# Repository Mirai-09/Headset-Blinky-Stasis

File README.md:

# Headset-Blinky-Stasis
This is Headset blinky that I made using a guide on Stasis, A YSWS from Hack Club!  

I made the PCB in the shape of Headset to match the Cassette PCB that I made before!

# Schematic!

# PCB!
Front: <br>

Back: <br>

3D: <br>

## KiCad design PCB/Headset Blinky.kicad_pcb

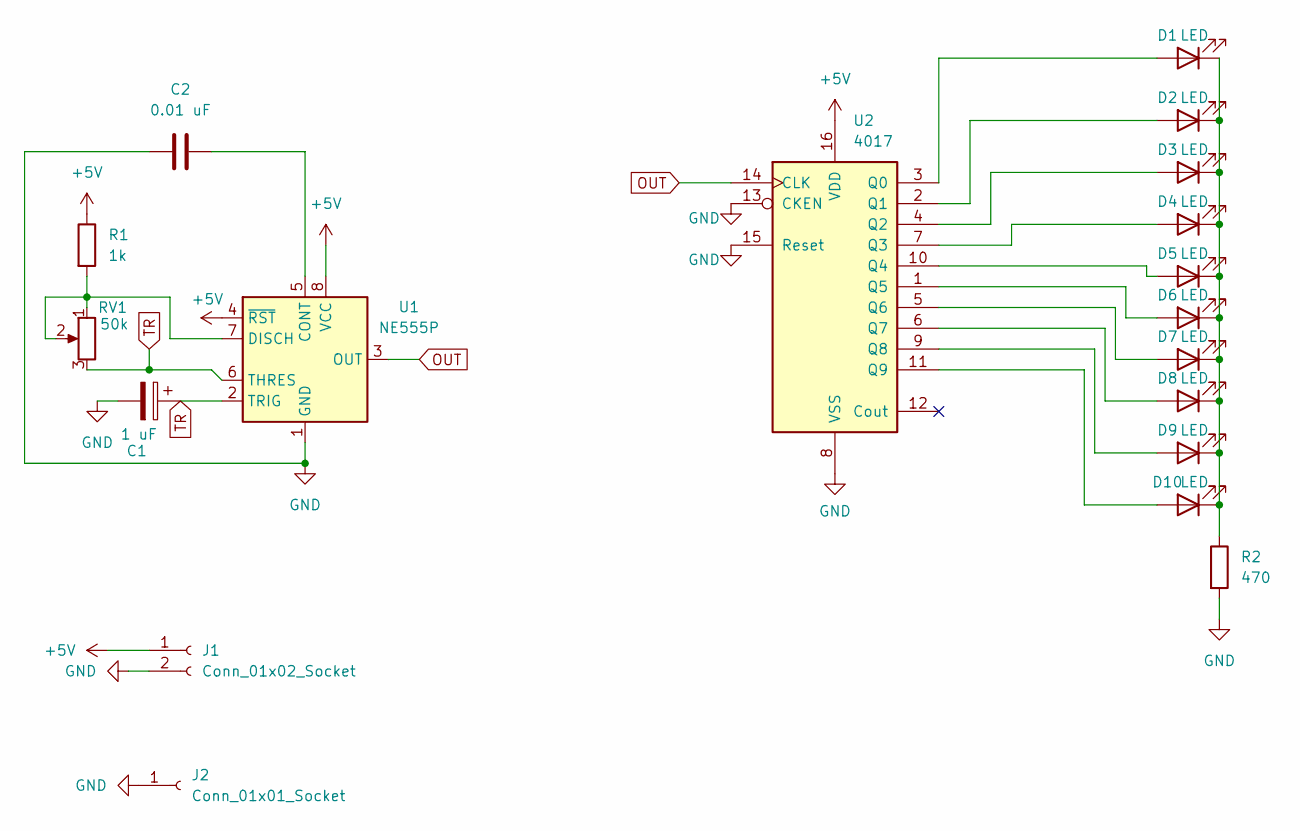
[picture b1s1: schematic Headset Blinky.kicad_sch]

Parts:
C1: 1 uF; CP_Radial_D5.0mm_P2.00mm
C2: 0.01 uF; C_Disc_D7.0mm_W2.5mm_P5.00mm
D1, D2, D3, D4, D5, D6, D7, D8, D9, D10: LED; LED_D3.0mm
J1: Conn_01x02_Socket; PinHeader_1x02_P2.54mm_Vertical
J2: Conn_01x01_Socket; PinHeader_1x01_P2.54mm_Vertical
R1: 1k; R_Axial_DIN0207_L6.3mm_D2.5mm_P7.62mm_Horizontal
R2: 470; R_Axial_DIN0207_L6.3mm_D2.5mm_P7.62mm_Horizontal
RV1: 50k; Potentiometer_Vishay_T93YA_Vertical
U1: NE555P; DIP-8_W7.62mm
U2: 4017; N16

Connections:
+5V: J1.1, R1.1, U1.4 (~RST), U1.8 (VCC), U2.16 (VDD)
GND: C1.2, C2.1, J1.2, J2.1, R2.2, U1.1 (GND), U2.8 (VSS), U2.13 (CKEN), U2.15 (Reset)
unnamed: D1.2 (A), U2.3 (Q0)
unnamed: D1.1 (K), D2.1 (K), D3.1 (K), D4.1 (K), D5.1 (K), D6.1 (K), D7.1 (K), D8.1 (K), D9.1 (K), D10.1 (K), R2.1
unnamed: D2.2 (A), U2.2 (Q1)
unnamed: D3.2 (A), U2.4 (Q2)
unnamed: D4.2 (A), U2.7 (Q3)
unnamed: D5.2 (A), U2.10 (Q4)
unnamed: D6.2 (A), U2.1 (Q5)
unnamed: D7.2 (A), U2.5 (Q6)
unnamed: D8.2 (A), U2.6 (Q7)
unnamed: D9.2 (A), U2.9 (Q8)
unnamed: D10.2 (A), U2.11 (Q9)
unnamed: C2.2, U1.5 (CONT)
unnamed: R1.2, RV1.1, RV1.2, U1.7 (DISCH)
OUT: U1.3 (OUT), U2.14 (CLK)
TR: C1.1, RV1.3, U1.2 (TRIG), U1.6 (THRES)

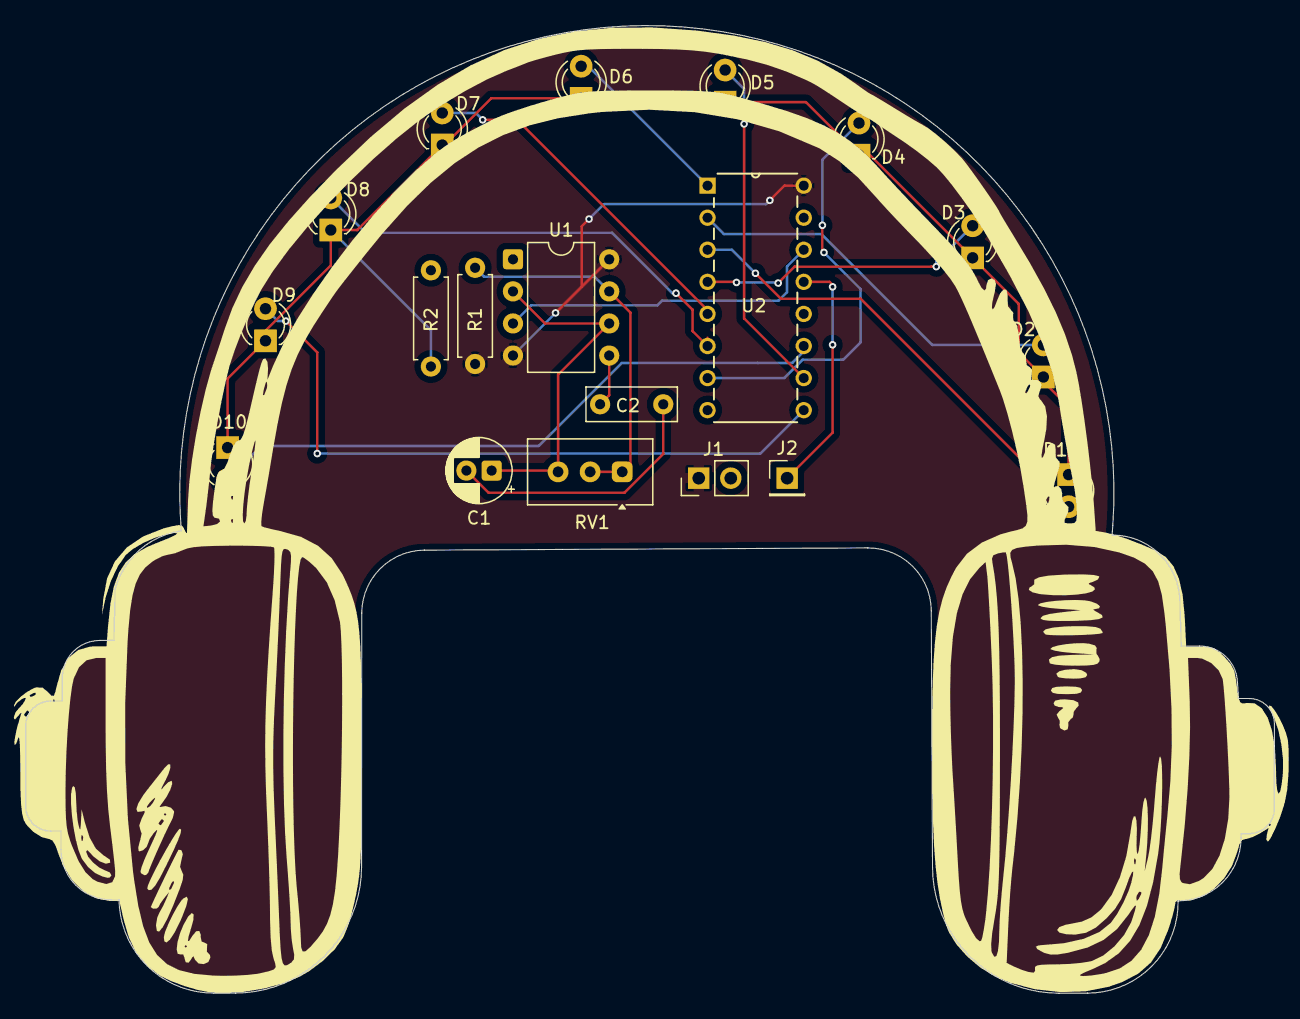
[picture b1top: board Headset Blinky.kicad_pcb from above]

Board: 2 copper layers, 98.9 x 76.6 mm, 20 parts (1 on the bottom side), 17 nets.

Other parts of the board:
a: LOGO

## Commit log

2026-04-03 Adding PCB files
    Unfinished routing
2026-04-04 Updated PCB files!
    Updated the routing - This will be the final routing of the PCB
2026-04-05 Updated PCB Files
    Updated routing and added art!
